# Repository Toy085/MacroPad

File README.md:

# Macropad

### Specifications
BOM:
- 6x Cherry MX Switches
- 6x Blank DSA Keycaps
- 3x SK6812 MINI-E LEDs
- 1x XIAO RP2040
- 1x 0.91 inch OLED display
- 4x M3x16 Bolt
- 4x M3 Heatset
- 1x RotaryEncoder_Alps_EC11E_Vertical_H20mm

Others:
- KMK Firmware
- MacroPad.step
- MacroPadTop.step

Schematic            |  PCB         |   Case
:-------------------------:|:-------------------------:|:-------------------------:|
 |  |

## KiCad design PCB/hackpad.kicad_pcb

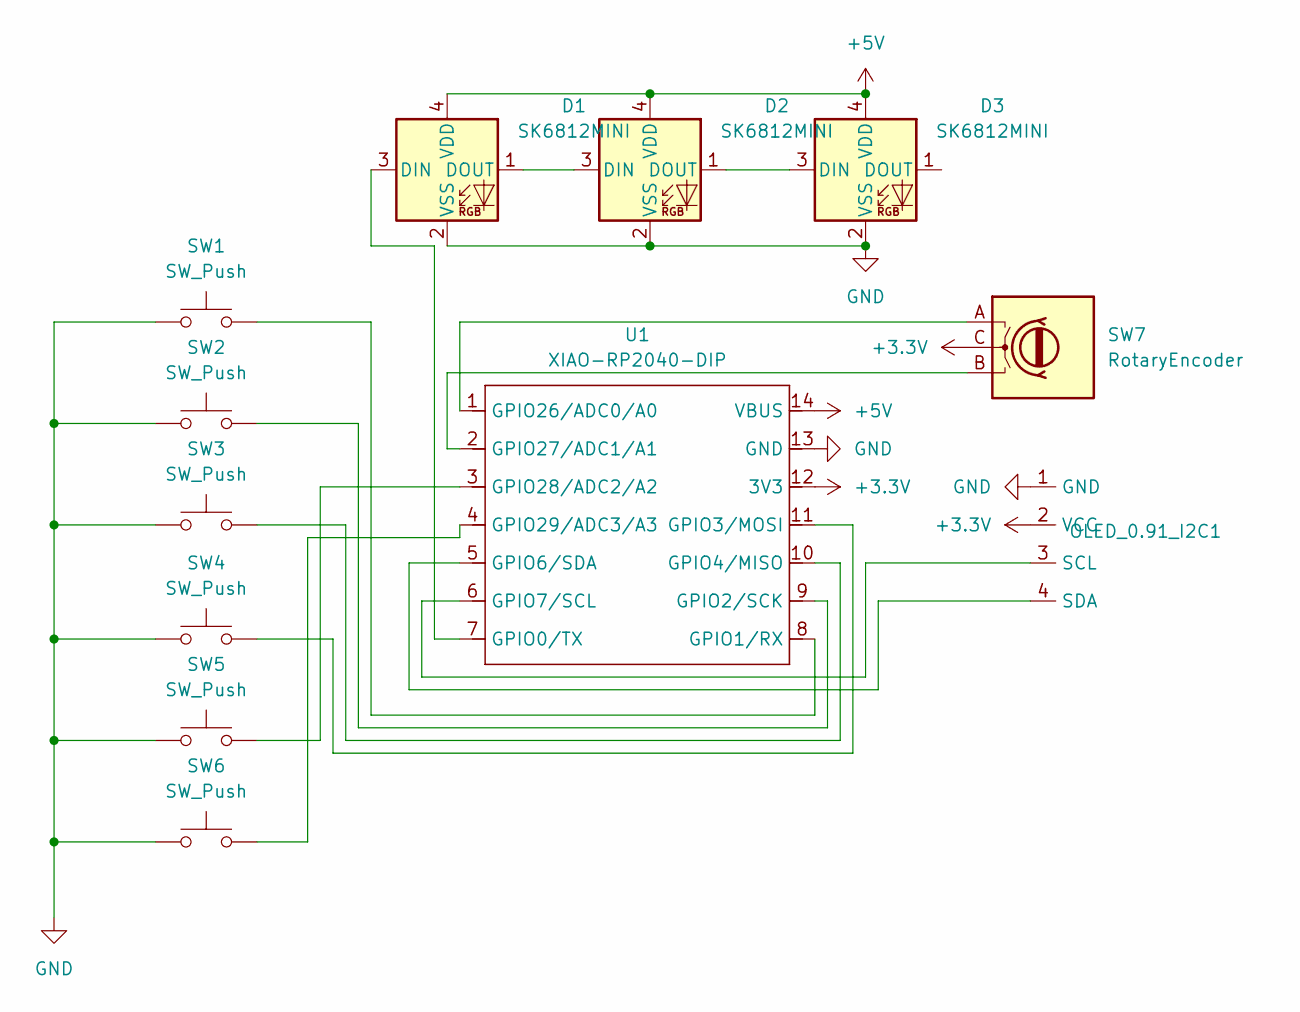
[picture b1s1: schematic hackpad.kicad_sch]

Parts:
D1, D2, D3: SK6812MINI; LED_SK6812MINI_PLCC4_3.5x3.5mm_P1.75mm
OLED_0.91_I2C1: SSD1306-0.91-OLED-4pin-128x32
SW1, SW2, SW3, SW4, SW5, SW6: SW_Push; SW_Cherry_MX_1.00u_PCB
SW7: RotaryEncoder; RotaryEncoder_Alps_EC11E_Vertical_H20mm
U1: XIAO-RP2040-DIP

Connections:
+3.3V: OLED_0.91_I2C1.2 (VCC), SW7.C, U1.12 (3V3)
+5V: D1.4 (VDD), D2.4 (VDD), D3.4 (VDD), U1.14 (VBUS)
GND: D1.2 (VSS), D2.2 (VSS), D3.2 (VSS), OLED_0.91_I2C1.1 (GND), SW1.1, SW2.1, SW3.1, SW4.1, SW5.1, SW6.1, U1.13 (GND)
unnamed: D1.3 (DIN), U1.7 (GPIO0/TX)
unnamed: D1.1 (DOUT), D2.3 (DIN)
unnamed: D2.1 (DOUT), D3.3 (DIN)
unnamed: OLED_0.91_I2C1.3 (SCL), U1.6 (GPIO7/SCL)
unnamed: OLED_0.91_I2C1.4 (SDA), U1.5 (GPIO6/SDA)
unnamed: SW1.2, U1.8 (GPIO1/RX)
unnamed: SW2.2, U1.9 (GPIO2/SCK)
unnamed: SW4.2, U1.11 (GPIO3/MOSI)
unnamed: SW3.2, U1.10 (GPIO4/MISO)
unnamed: SW7.A, U1.1 (GPIO26/ADC0/A0)
unnamed: SW7.B, U1.2 (GPIO27/ADC1/A1)
unnamed: SW5.2, U1.3 (GPIO28/ADC2/A2)
unnamed: SW6.2, U1.4 (GPIO29/ADC3/A3)

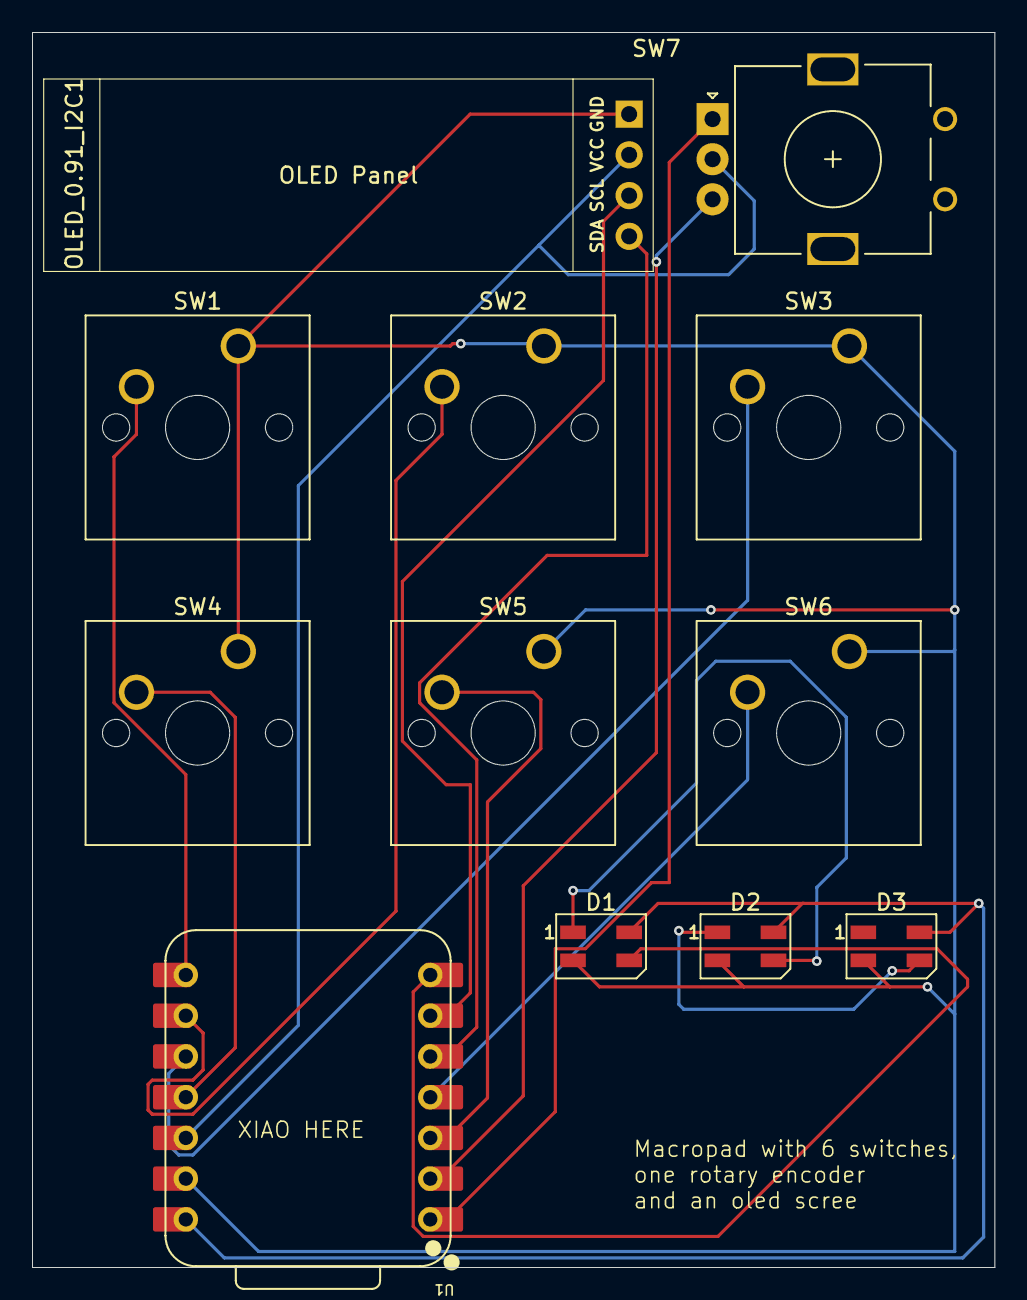
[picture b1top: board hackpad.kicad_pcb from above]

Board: 2 copper layers, 60.0 x 77.0 mm, 12 parts (0 on the bottom side), 16 nets.

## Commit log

2025-11-23 Create CAD
2025-11-23 Create temp
2025-11-23 Initialize KMK keyboard firmware in main.py
2025-11-23 Add Macropad specifications to README
    Added specifications and components for the Macropad.
2025-11-23 Fix duplicate BOM entry for Blank DSA Keycaps
    Removed duplicate entry for Blank DSA Keycaps in BOM.
2025-11-24 Update images in README.md
    Updated images in the README for better clarity.
2025-11-24 Fix LED naming in specifications
2025-12-15 Update keyboard keymap with new keycodes
2025-12-15 Update pin assignments for keyboard module
